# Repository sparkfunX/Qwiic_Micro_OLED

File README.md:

# Qwiic_Micro_OLED
========================================

[*SPX-14269*](https://www.sparkfun.com/products/14269)

The Qwiic Micro OLED is a small monochrome, blue-on-black OLED. It’s "micro", but it still packs a punch – the OLED display is crisp, and you can fit a deceivingly large amount of graphics on there. This breakout is perfect for adding graphics to your next project or displaying diagnostic information without resorting to serial output.

The Qwiic version of the Micro OLED has two Qwiic connectors that allow you to easily and quickly attach the display to the Qwicc Shield of your choosing.The [Qwiic system](http://www.sparkfun.com/qwiic) enables fast and solderless connection between popular platforms and various sensors and actuators. You can read more about the Qwiic system [here](http://www.sparkfun.com/qwiic). 

License Information
-------------------

This product is _**open source**_!

Please review the LICENSE.md file for license information.

If you have any questions or concerns on licensing, please contact techsupport@sparkfun.com.

Distributed as-is; no warranty is given.

- Your friends at SparkFun.

_<COLLABORATION CREDIT>_

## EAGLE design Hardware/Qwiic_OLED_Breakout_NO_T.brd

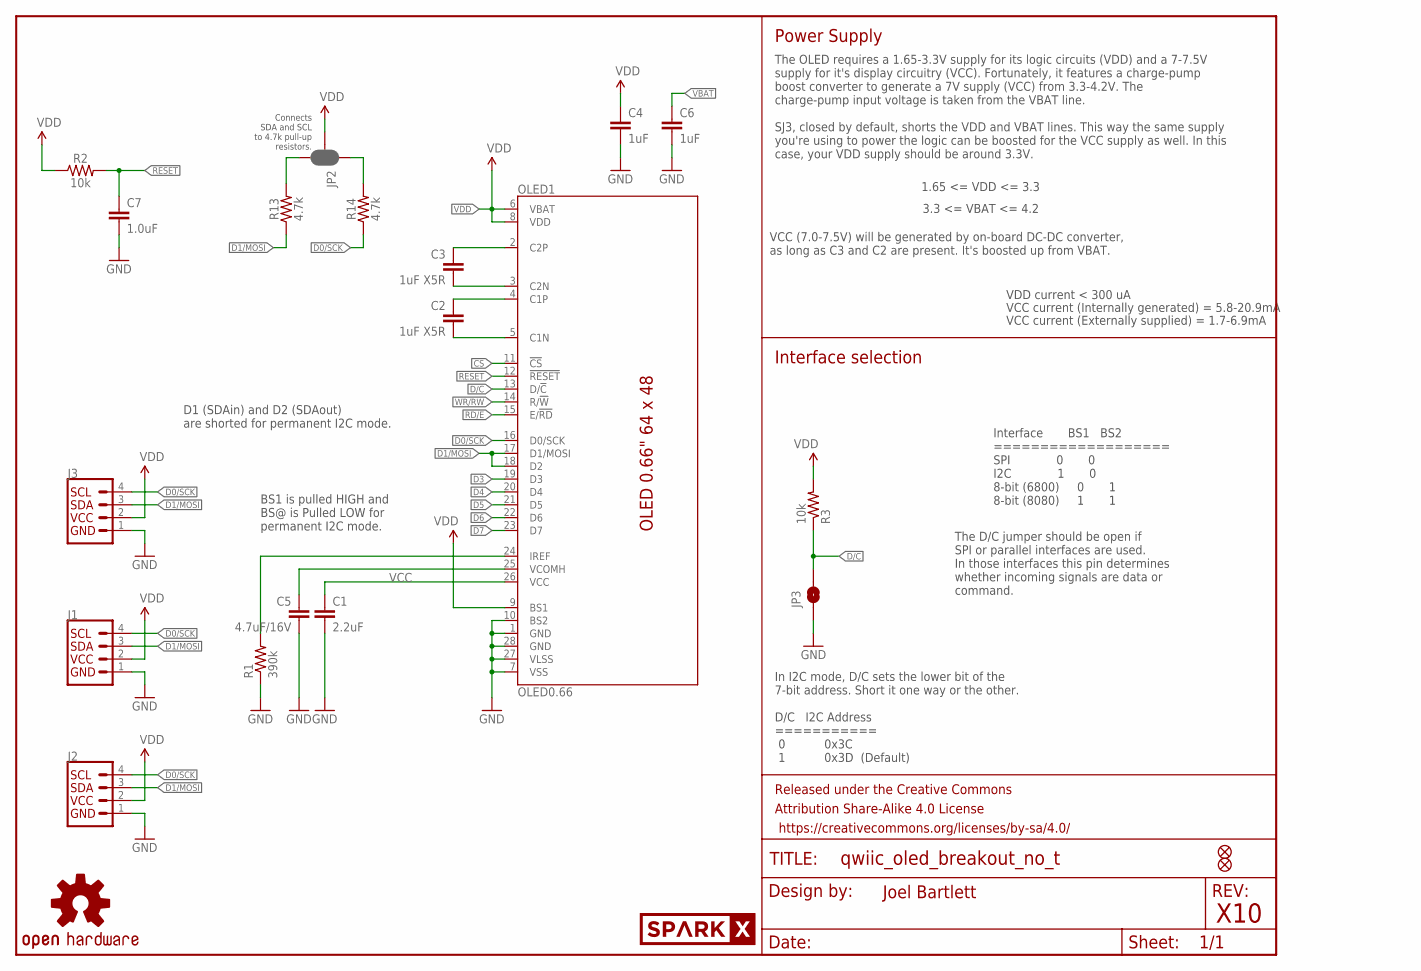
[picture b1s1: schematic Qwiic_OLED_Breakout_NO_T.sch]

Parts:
C1: 2.2uF; 0805
C2, C3: 1uF X5R; 0805
C4, C6: 1uF; 0603-CAP
C5: 4.7uF/16V; 1206
C7: 1.0uF; 0603
FID1, FID2: FIDUCIAL1X2; FIDUCIAL-1X2
FRAME1: FRAME-LETTER; CREATIVE_COMMONS
J1, J2: I2C_STANDARDJS-1MM; 1X04_1MM_RA
J3: I2C_STANDARD_NO_SILK; 1X04_NO_SILK
JP2: JUMPER-SMT_3_2-NC_PASTE_SILK; SMT-JUMPER_3_2-NC_PASTE_SILK
JP3: JUMPER-SMT_2_NO_SILK; SMT-JUMPER_2_NO_SILK
LOGO3: OSHW-LOGOS; OSHW-LOGO-S
OLED1: OLED0.66; OLED-0.66-64X48
R1: 390k; 0603-RES
R2: 10k; 0603
R3: 10k; 0603-RES
R13, R14: 4.7k; 0603
U$3: SPARKX-LOGO2; SPARKX-TINY

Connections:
C1N: C2.2, OLED1.5 (C1N)
C1P: C2.1, OLED1.4 (C1P)
C2N: C3.2, OLED1.3 (C2N)
C2P: C3.1, OLED1.2 (C2P)
CS: OLED1.11 (!CS!)
D0/SCK: J1.4 (SCL), J2.4 (SCL), J3.4 (SCL), OLED1.16 (D0/SCK), R14.1
D1/MOSI: J1.3 (SDA), J2.3 (SDA), J3.3 (SDA), OLED1.17 (D1/MOSI), OLED1.18 (D2), R13.1
D3: OLED1.19 (D3)
D4: OLED1.20 (D4)
D5: OLED1.21 (D5)
D6: OLED1.22 (D6)
D7: OLED1.23 (D7)
D/C: JP3.2, OLED1.13 (D/!C!), R3.1
GND: C1.2, C4.2, C5.2, C6.2, C7.2, J1.1 (GND), J2.1 (GND), J3.1 (GND), JP3.1, OLED1.1 (GND), OLED1.7 (VSS), OLED1.10 (BS2), OLED1.27 (VLSS), OLED1.28 (GND), R1.1
IREF: OLED1.24 (IREF), R1.2
unnamed: JP2.3, R13.2
unnamed: JP2.1, R14.2
RD/E: OLED1.15 (E/!RD!)
RESET: C7.1, OLED1.12 (!RESET!), R2.2
VBAT: C6.1
VCC: C1.1, OLED1.26 (VCC)
VCOMH: C5.1, OLED1.25 (VCOMH)
VDD: C4.1, J1.2 (VCC), J2.2 (VCC), J3.2 (VCC), JP2.2, OLED1.6 (VBAT), OLED1.8 (VDD), OLED1.9 (BS1), R2.1, R3.2
WR/RW: OLED1.14 (R/!W!)

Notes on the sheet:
X10
1.65 <= VDD <= 3.3
VDD current < 300 uA
VCC current (Internally generated) = 5.8-20.9mA
VCC current (Externally supplied) = 1.7-6.9mA
Interface BS1 BS2 =================== SPI 0 0 I2C 1 0 8-bit (6800) 0 1 8-bit (8080) 1 1
VCC (7.0-7.5V) will be generated by on-board DC-DC converter, as long as C3 and C2 are present. It's boosted up from VBAT.
3.3 <= VBAT <= 4.2
Interface selection
D1 (SDAin) and D2 (SDAout) are shorted for permanent I2C mode.
In I2C mode, D/C sets the lower bit of the 7-bit address. Short it one way or the other. D/C I2C Address =========== 0 0x3C 1 0x3D (Default)
Power Supply
The OLED requires a 1.65-3.3V supply for its logic circuits (VDD) and a 7-7.5V supply for it's display circuitry (VCC). Fortunately, it features a charge-pump boost converter to generate a 7V supply (VCC) from 3.3-4.2V. The charge-pump input voltage is taken from the VBAT line. SJ3, closed by defau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
The D/C jumper should be open if SPI or parallel interfaces are used. In those interfaces this pin determines whether incoming signals are data or command.
BS1 is pulled HIGH and BS@ is Pulled LOW for permanent I2C mode.
Connects SDA and SCL to 4.7k pull-up resistors.
Joel Bartlett

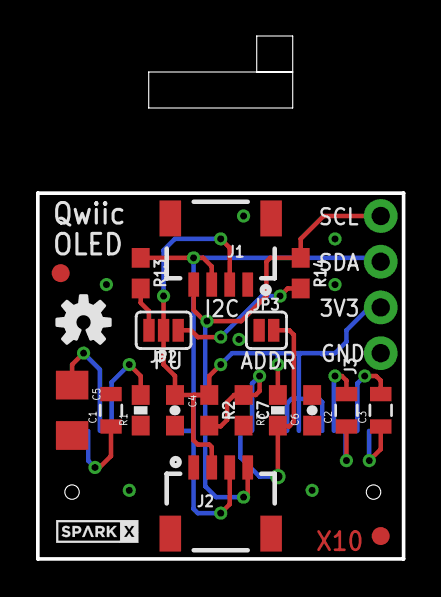
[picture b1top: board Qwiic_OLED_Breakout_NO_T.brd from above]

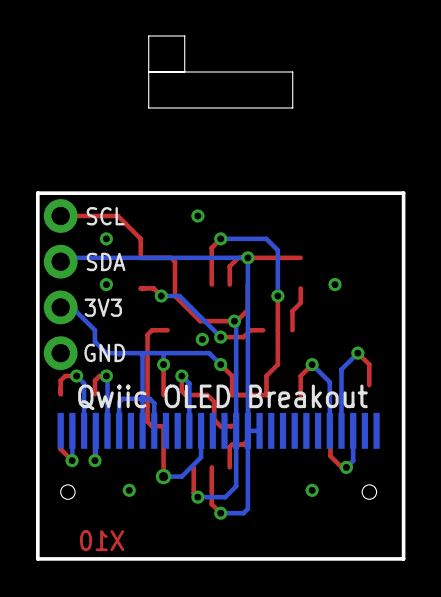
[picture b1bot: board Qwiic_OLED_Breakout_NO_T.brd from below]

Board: 2 copper layers, 20.3 x 20.3 mm, 23 parts (2 on the bottom side), 15 nets.

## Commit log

2017-03-14 More mold modifications Elongated the PCB for mold
2017-03-16 Mold V2
2017-03-31 Adding Gerbers
2017-04-08 Adding build pdf
2017-04-11 Added soldering jig
2017-04-12 Adding product page files
2017-04-12 Updating gitignore
2017-04-12 cleanup
2017-04-12 Cleanup repo
2017-04-14 Adding suction cup holder

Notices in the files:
parts and their libraries:
SparkFun-Aesthetics: Licensing: Creative Commons ShareAlike 4.0 International - https://creativecommons.org/licenses/by-sa/4.0
SparkFun-Aesthetics: Released under the Creative Commons Attribution Share-Alike 4.0 License
SparkFun-Aesthetics: https://creativecommons.org/licenses/by-sa/4.0
